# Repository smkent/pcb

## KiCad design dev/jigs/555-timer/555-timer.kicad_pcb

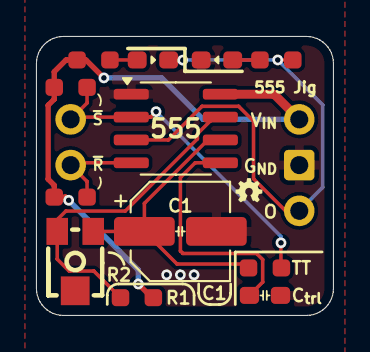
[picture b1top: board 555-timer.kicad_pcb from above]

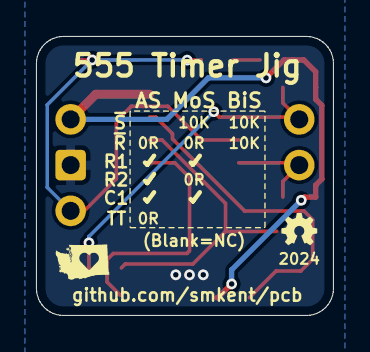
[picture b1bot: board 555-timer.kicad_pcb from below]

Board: 2 copper layers, 16.5 x 15.5 mm, 14 parts (2 on the bottom side), 10 nets.

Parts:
C0: 0u1; C_0603_1608Metric_Pad1.08x0.95mm_HandSolder
C1: 1u; C_Combo_CP_Elec_5x5.4
J1: Pin headers; PinHeader_1x03_P2.54mm_Vertical_simple_pad2gnd
J2: Pin headers; PinHeader_1x02_P2.54mm_Vertical_simple
LED1, LED2: LED_Small; LED_0603_1608Metric_Pad1.05x0.95mm_HandSolder_simple
R0, R3, R4: 0R; R_0603_1608Metric_Pad0.98x0.95mm_HandSolder_simple
R1: 10K; R_0603_1608Metric_Pad0.98x0.95mm_HandSolder_simple
R5, R6: 1K; R_0603_1608Metric_Pad0.98x0.95mm_HandSolder_simple
RV1: 500K; RES-ADJ-SMD_VG039NCH
U1: NE555; SOIC-8_3.9x4.9mm_P1.27mm

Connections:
+5V: J1.1, R0.2, R1.1, R4.2, R5.1, U1.8 (VCC)
GND: C0.2, C1.2, J1.2, LED2.1 (K), U1.1 (GND)
unnamed: LED1.2 (A), R5.2
unnamed: LED2.2 (A), R6.2
unnamed: C0.1, U1.5 (Control)
unnamed: R1.2, RV1.3, U1.7 (Discharge)
unnamed: C1.1, R3.2, RV1.1, U1.6 (Threshold)
Output: J1.3, LED1.1 (K), R6.1, U1.3 (Output)
~R: J2.2, R0.1, U1.4 (~Reset)
~S: J2.1, R3.1, R4.1, U1.2 (Trigger)

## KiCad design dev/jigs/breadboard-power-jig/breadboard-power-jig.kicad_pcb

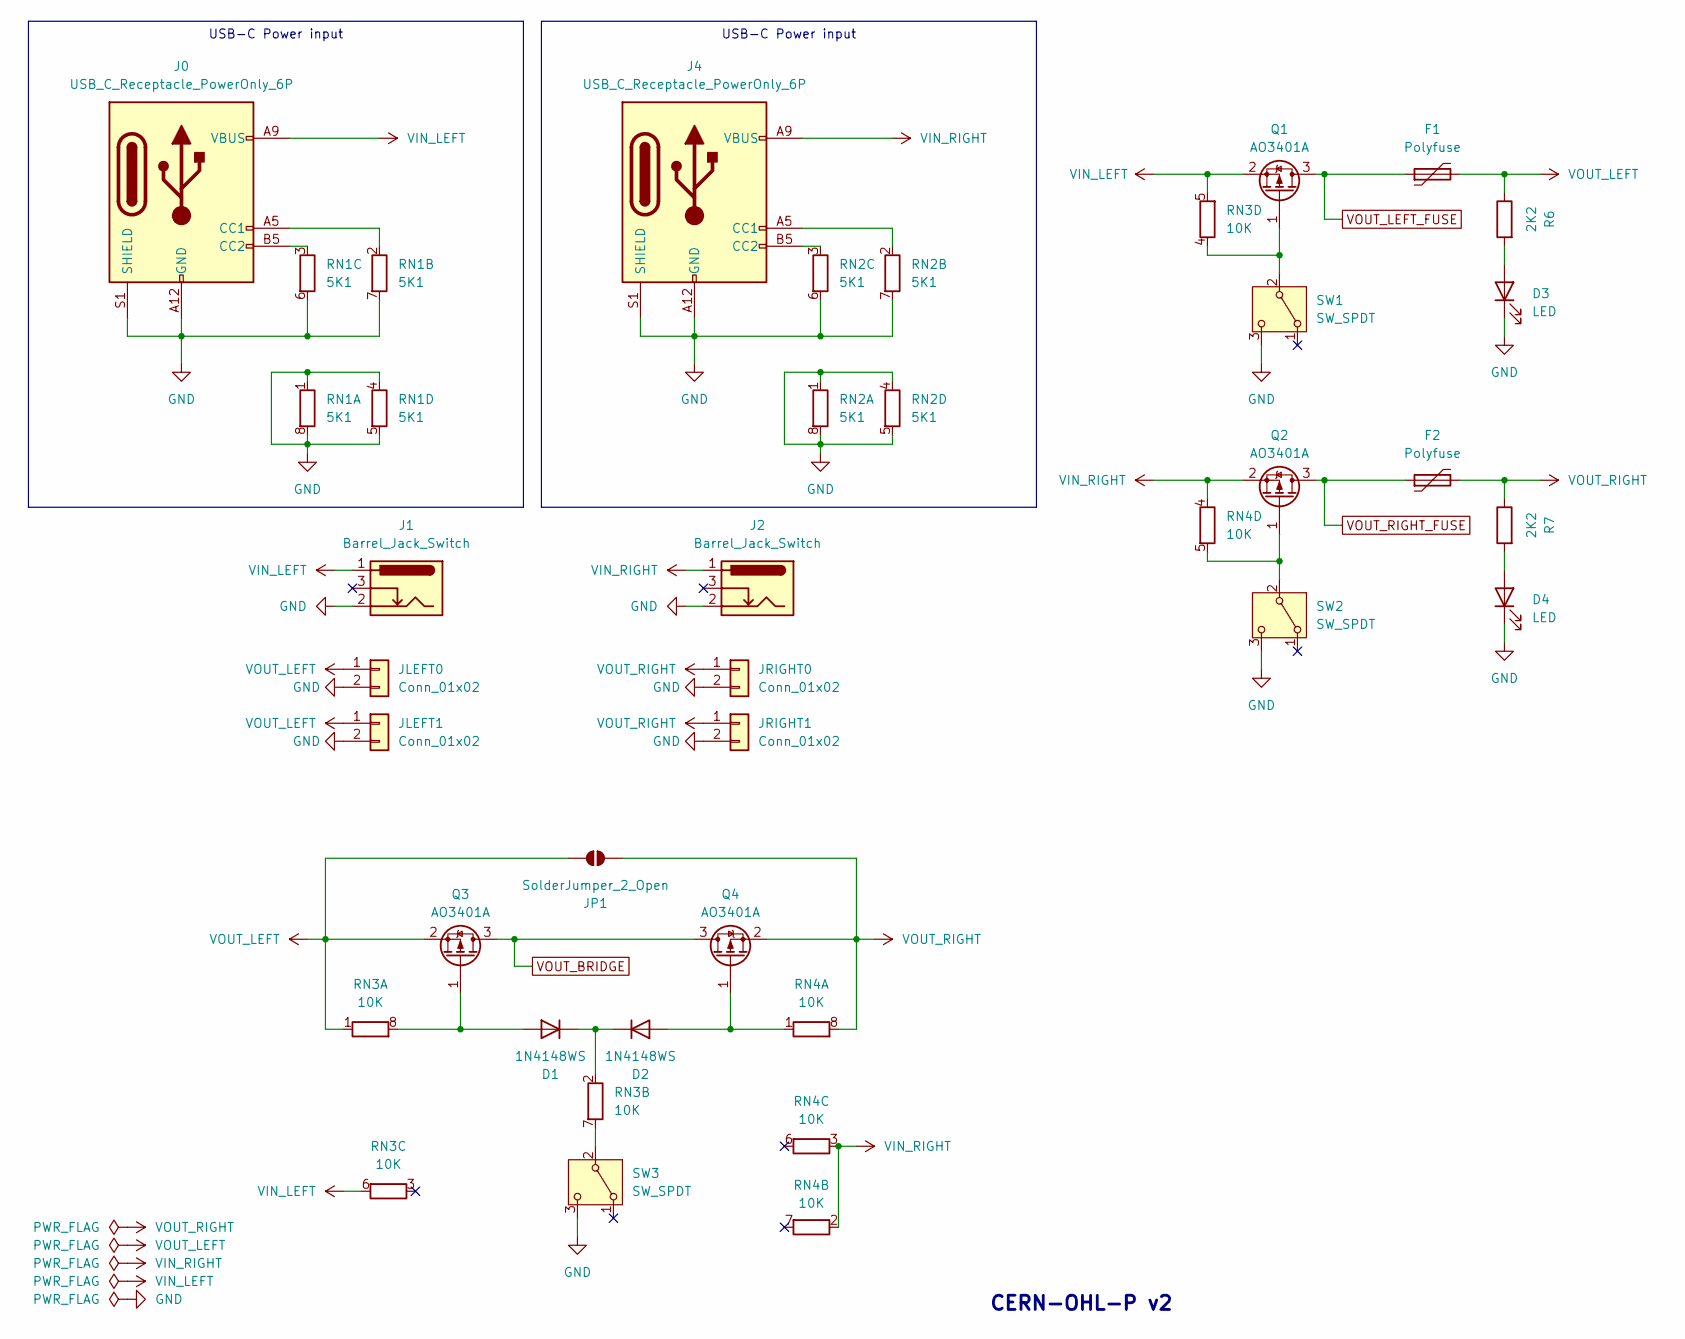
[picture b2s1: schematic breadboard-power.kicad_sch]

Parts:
D1, D2: 1N4148WS; D_SOD-323_HandSoldering_simple
D3, D4: LED; LED_0805_2012Metric_Pad1.15x1.40mm_HandSolder_simple
F1, F2: Polyfuse; Fuse_1206_3216Metric_Pad1.42x1.75mm_HandSolder_simple
J0, J4: USB_C_Receptacle_PowerOnly_6P; USB_C_Receptacle_GCT_USB4125-xx-x_6P_TopMnt_Horizontal_hand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
J1, J2: Barrel_Jack_Switch; Conn_Combo_DC-050_TerminalBlock_JST-XH-2P-horizontal-TH-or-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
JLEFT0, JLEFT1: Conn_01x02; PinHeader_1x02_P2.54mm_Vertical_simple_pad2gnd
JP1: SolderJumper_2_Open; SolderJumper-2_P1.3mm_Open_RoundedPad1.0x1.5mm_simple
JRIGHT0, JRIGHT1: Conn_01x02; PinHeader_1x02_P2.54mm_Vertical_simple_pad2gnd
Q1, Q2, Q3, Q4: AO3401A; SOT-23; LCSC Part C15127
R6, R7: 2K2; R_0805_2012Metric_Pad1.20x1.40mm_HandSolder
RN1, RN2: 5K1; R_Array_Convex_4x0603
RN3, RN4: 10K; R_Array_Convex_4x0603
SW1, SW2: SW_SPDT; SW-TH_DEALON_SS-12D01-GX_simple; LCSC Part C2998803
SW3: SW_SPDT; SW-SMD_3P-P1.50_L2.7-W6.6; LCSC Part C2998803

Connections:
GND: D3.1 (K), D4.1 (K), J0.A12 (GND), J0.B12 (GND), J0.S1 (SHIELD), J1.2, J2.2, J4.A12 (GND), J4.B12 (GND), J4.S1 (SHIELD), JLEFT0.2, JLEFT1.2, JRIGHT0.2, JRIGHT1.2, RN1.1 (R1.1), RN1.4 (R4.1), RN1.5 (R4.2), RN1.6 (R3.2), RN1.7 (R2.2), RN1.8 (R1.2), RN2.1 (R1.1), RN2.4 (R4.1), RN2.5 (R4.2), RN2.6 (R3.2), RN2.7 (R2.2), RN2.8 (R1.2), SW1.3 (C), SW2.3 (C), SW3.3 (C)
unnamed: D1.2 (A), Q3.1 (G), RN3.8 (R1.2)
unnamed: D1.1 (K), D2.1 (K), RN3.2 (R2.1)
unnamed: D2.2 (A), Q4.1 (G), RN4.1 (R1.1)
unnamed: D3.2 (A), R6.2
unnamed: D4.2 (A), R7.2
unnamed: J0.A5 (CC1), RN1.2 (R2.1)
unnamed: J0.B5 (CC2), RN1.3 (R3.1)
unnamed: J4.A5 (CC1), RN2.2 (R2.1)
unnamed: J4.B5 (CC2), RN2.3 (R3.1)
unnamed: Q1.1 (G), RN3.4 (R4.1), SW1.2 (B)
unnamed: Q2.1 (G), RN4.5 (R4.2), SW2.2 (B)
unnamed: RN3.7 (R2.2), SW3.2 (B)
VIN_LEFT: J0.A9 (VBUS), J0.B9 (VBUS), J1.1, Q1.2 (S), RN3.5 (R4.2), RN3.6 (R3.2)
VIN_RIGHT: J2.1, J4.A9 (VBUS), J4.B9 (VBUS), Q2.2 (S), RN4.2 (R2.1), RN4.3 (R3.1), RN4.4 (R4.1)
VOUT_BRIDGE: Q3.3 (D), Q4.3 (D)
VOUT_LEFT: F1.2, JLEFT0.1, JLEFT1.1, JP1.1 (A), Q3.2 (S), R6.1, RN3.1 (R1.1)
VOUT_LEFT_FUSE: F1.1, Q1.3 (D)
VOUT_RIGHT: F2.2, JP1.2 (B), JRIGHT0.1, JRIGHT1.1, Q4.2 (S), R7.1, RN4.8 (R1.2)
VOUT_RIGHT_FUSE: F2.1, Q2.3 (D)

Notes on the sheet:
USB-C Power input
CERN-OHL-P v2

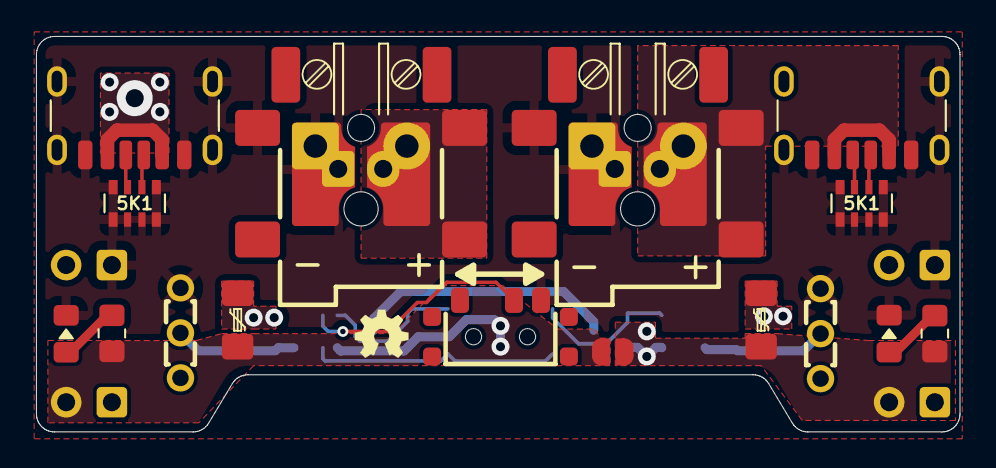
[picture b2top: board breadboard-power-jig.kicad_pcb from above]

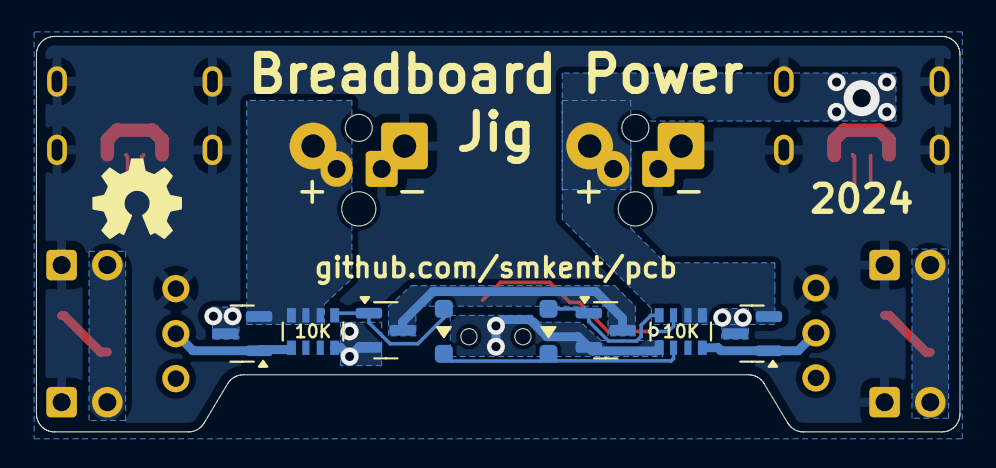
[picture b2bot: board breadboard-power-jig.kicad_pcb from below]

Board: 2 copper layers, 51.3 x 22.0 mm, 28 parts (12 on the bottom side), 20 nets.

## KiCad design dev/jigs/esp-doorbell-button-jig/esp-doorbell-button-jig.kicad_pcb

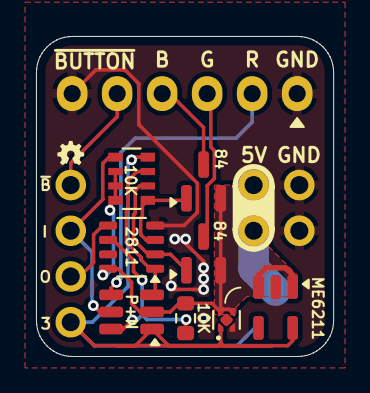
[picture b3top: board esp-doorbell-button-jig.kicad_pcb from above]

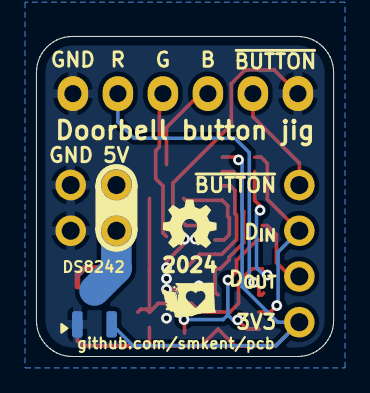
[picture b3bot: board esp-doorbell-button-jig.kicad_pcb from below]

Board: 2 copper layers, 16.5 x 17.8 mm, 12 parts (3 on the bottom side), 13 nets.

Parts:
J1: Pin headers; PinHeader_1x04_P2.54mm_Vertical_simple
J3: JST XH; JST_XH_B6B-XH-A_1x06_P2.50mm_Vertical_slim
J4: Pin Headers; PinHeader_2x02_P2.54mm_Vertical_simple
Q1, Q2: BSS84; SOT-23_simple
Q3: G1NP02LLE; SOT-23-6_simple
R5: 10K; R_0603_1608Metric
RN1: 10K; R_Array_Convex_4x0603
U1: WS2811F; FSOP-8_L3.3-W1.7-P0.80-LS2.9-BL
U2: DS8242-50SS3; SOT-23_simple
U3: Texas_X2SON-4_1x1mm_P0.65mm
U4: ME6211C33M5; SOT-23-5_simple

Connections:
+3V3: J1.4, Q3.1 (G), RN1.4 (R4.1), U2.2 (VO), U3.1, U4.5 (V_{OUT})
+5V: J4.1, J4.3, Q1.2 (S), Q2.2 (S), Q3.2 (S), R5.2, RN1.6 (R3.2), RN1.7 (R2.2), RN1.8 (R1.2), U1.8 (VDD), U2.3 (VI), U3.3, U3.4, U4.1 (V_{IN}), U4.3 (CE)
BUTTON: J1.1, J3.5
BUTTON_LED_B: J3.4, Q1.3 (D)
BUTTON_LED_B_EN: Q1.1 (G), RN1.1 (R1.1), U1.3 (OUTB)
BUTTON_LED_G: J3.3, Q2.3 (D)
BUTTON_LED_G_EN: Q2.1 (G), RN1.2 (R2.1), U1.2 (OUTG)
BUTTON_LED_R: J3.2, Q3.4 (D)
BUTTON_LED_R_EN: Q3.3 (G), RN1.3 (R3.1), U1.1 (OUTR)
DATA_IN: Q3.6 (D), R5.1, U1.6 (DIN)
DATA_IN_3V3: J1.2, Q3.5 (S), RN1.5 (R4.2)
DATA_OUT: J1.3, U1.5 (DO)
GND: J3.1, J3.6, J4.2, J4.4, U1.4 (GND), U2.1 (GND), U3.2, U4.2 (V_{SS})

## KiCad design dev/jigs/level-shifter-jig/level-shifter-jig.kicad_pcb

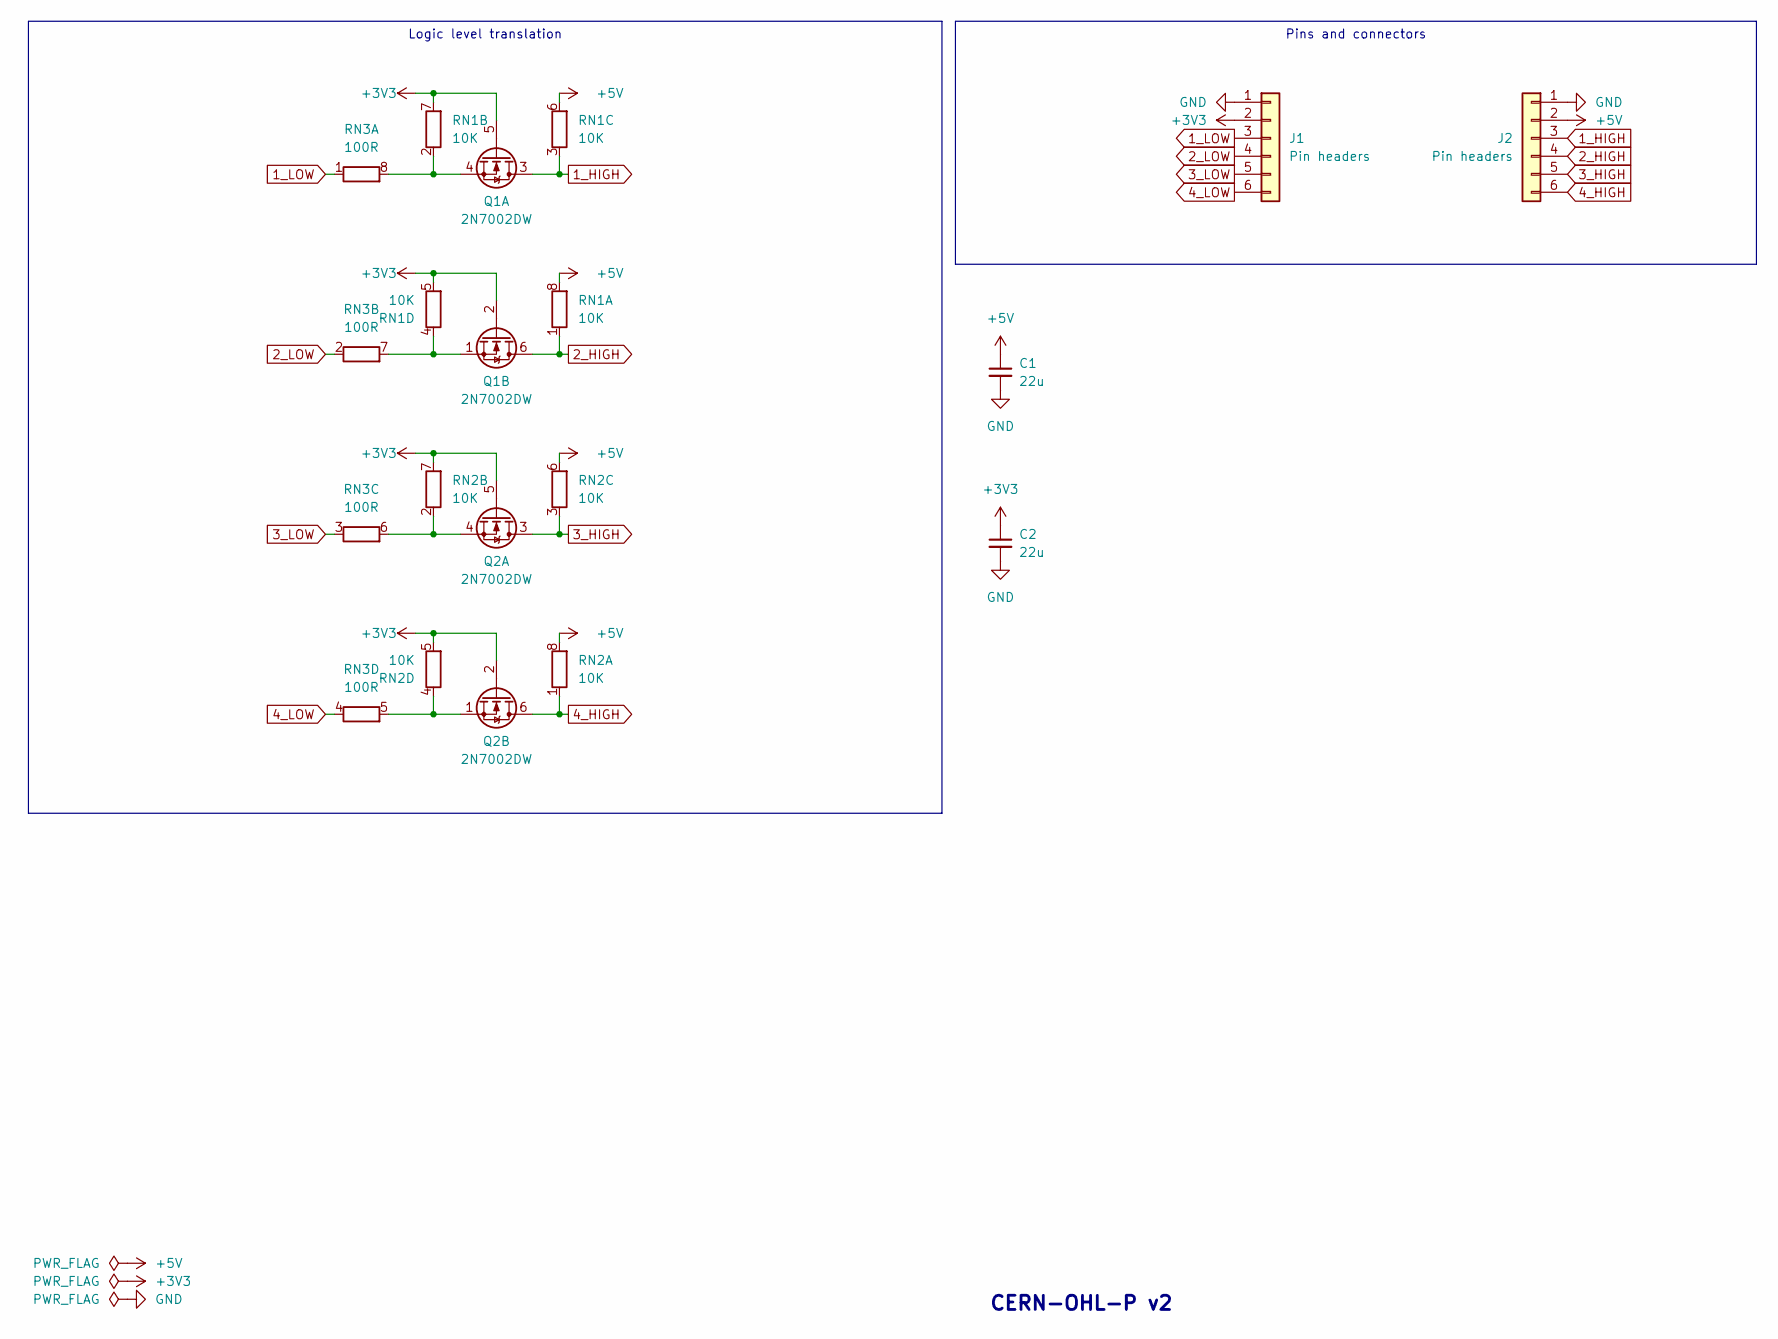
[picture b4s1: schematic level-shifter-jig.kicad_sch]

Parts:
C1, C2: 22u; C_0603_1608Metric_Pad1.08x0.95mm_HandSolder
J1, J2: Pin headers; PinHeader_1x06_P2.54mm_Vertical_simple_pad1gnd
Q1, Q2: 2N7002DW; SOT-363_SC-70-6_simple; LCSC Part C5190214
RN1, RN2: 10K; R_Array_Convex_4x0603
RN3: 100R; R_Array_Convex_4x0603

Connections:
1_HIGH: J2.3, Q1.3 (D), RN1.3 (R3.1)
1_LOW: J1.3, RN3.1 (R1.1)
2_HIGH: J2.4, Q1.6 (D), RN1.1 (R1.1)
2_LOW: J1.4, RN3.2 (R2.1)
3_HIGH: J2.5, Q2.3 (D), RN2.3 (R3.1)
3_LOW: J1.5, RN3.3 (R3.1)
4_HIGH: J2.6, Q2.6 (D), RN2.1 (R1.1)
4_LOW: J1.6, RN3.4 (R4.1)
+3V3: C2.1, J1.2, Q1.2 (G), Q1.5 (G), Q2.2 (G), Q2.5 (G), RN1.5 (R4.2), RN1.7 (R2.2), RN2.5 (R4.2), RN2.7 (R2.2)
+5V: C1.1, J2.2, RN1.6 (R3.2), RN1.8 (R1.2), RN2.6 (R3.2), RN2.8 (R1.2)
GND: C1.2, C2.2, J1.1, J2.1
unnamed: Q1.4 (S), RN1.2 (R2.1), RN3.8 (R1.2)
unnamed: Q1.1 (S), RN1.4 (R4.1), RN3.7 (R2.2)
unnamed: Q2.4 (S), RN2.2 (R2.1), RN3.6 (R3.2)
unnamed: Q2.1 (S), RN2.4 (R4.1), RN3.5 (R4.2)

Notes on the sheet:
Pins and connectors
Logic level translation
CERN-OHL-P v2

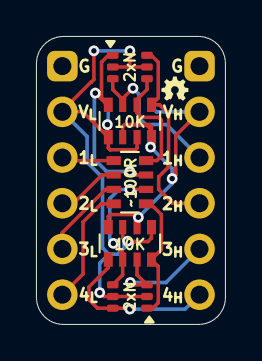
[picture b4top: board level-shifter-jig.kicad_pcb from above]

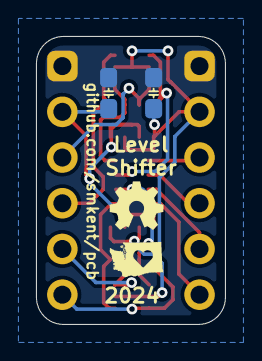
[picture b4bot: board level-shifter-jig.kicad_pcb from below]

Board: 2 copper layers, 10.5 x 16.0 mm, 9 parts (4 on the bottom side), 15 nets.

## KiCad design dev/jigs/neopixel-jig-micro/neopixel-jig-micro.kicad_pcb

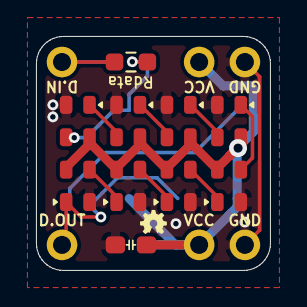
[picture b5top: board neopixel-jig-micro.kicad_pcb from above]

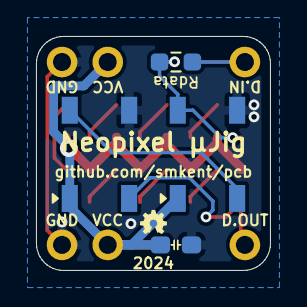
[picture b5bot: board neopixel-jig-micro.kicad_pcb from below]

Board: 2 copper layers, 13.0 x 13.0 mm, 18 parts (8 on the bottom side), 13 nets.

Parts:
C1, C2: 10u; C_0603_1608Metric_Pad1.08x0.95mm_HandSolder
D1, D2: WS2812B; LED_WS2812B_PLCC4_5.0x5.0mm_P3.2mm_simple_small_courtyard
J1, J2: Conn_01x02; PinHeader_1x02_P2.54mm_Vertical_simple
J3, J4: Conn_01x01; PinHeader_1x01_P2.54mm_simple
LED1, LED2, LED3, LED4, LED5, LED6, LED7, LED8: WS2812B-2020; LED-SMD_4P-L2.0-W2.0-BR-1
R1, R2: 100R; R_0603_1608Metric_Pad0.98x0.95mm_HandSolder

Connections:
DATA_2: LED4.1 (DOUT), LED5.3 (DIN)
DATA_IN: D1.4 (DIN), LED1.3 (DIN), R1.2, R2.2
DATA_OUT: D2.2 (DOUT), J4.1, LED8.1 (DOUT)
GND: C1.2, C2.2, D1.3 (VSS), D2.3 (VSS), J1.2, J2.2, LED1.2 (VSS), LED2.2 (VSS), LED3.2 (VSS), LED4.2 (VSS), LED5.2 (VSS), LED6.2 (VSS), LED7.2 (VSS), LED8.2 (VSS)
unnamed: D1.2 (DOUT), D2.4 (DIN)
unnamed: J3.1, R1.1, R2.1
unnamed: LED1.1 (DOUT), LED2.3 (DIN)
unnamed: LED2.1 (DOUT), LED3.3 (DIN)
unnamed: LED3.1 (DOUT), LED4.3 (DIN)
unnamed: LED5.1 (DOUT), LED6.3 (DIN)
unnamed: LED6.1 (DOUT), LED7.3 (DIN)
unnamed: LED7.1 (DOUT), LED8.3 (DIN)
VCC: C1.1, C2.1, D1.1 (VDD), D2.1 (VDD), J1.1, J2.1, LED1.4 (VDD), LED2.4 (VDD), LED3.4 (VDD), LED4.4 (VDD), LED5.4 (VDD), LED6.4 (VDD), LED7.4 (VDD), LED8.4 (VDD)

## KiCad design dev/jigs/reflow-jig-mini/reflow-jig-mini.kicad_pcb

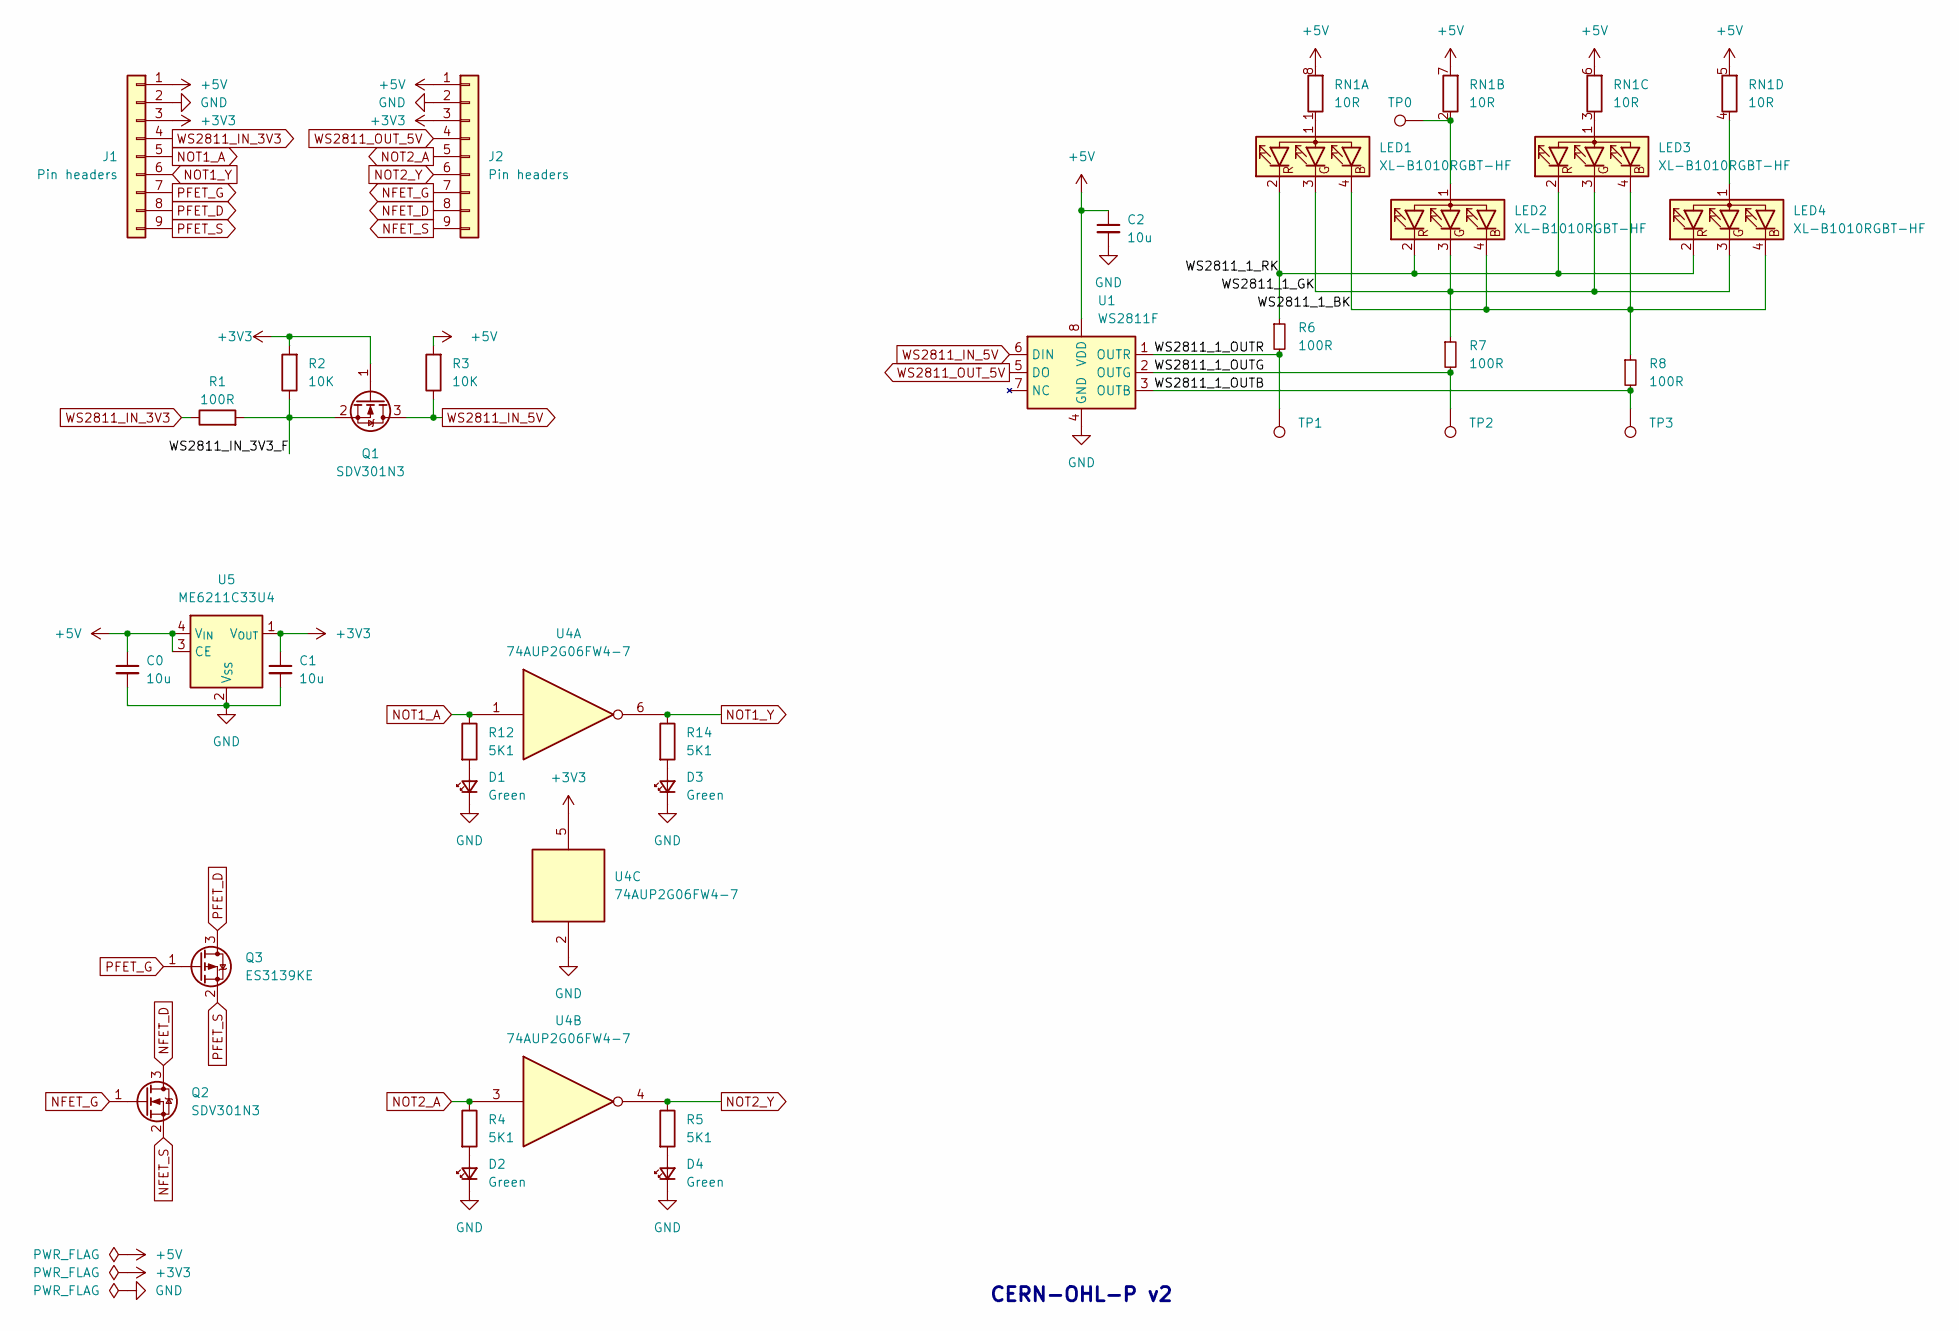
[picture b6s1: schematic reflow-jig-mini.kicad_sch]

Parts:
C0, C1, C2: 10u; C_0402_1005Metric_simple
D1, D2, D3, D4: Green; LED_0402_1005Metric
J1, J2: Pin headers; PinHeader_1x09_P2.54mm_Vertical_simple
LED1, LED2, LED3, LED4: XL-B1010RGBT-HF; LED-ARRAY-SMD_4P-L1.0-W1.0-TR-RD
Q1, Q2: SDV301N3; DFN1006-3; LCSC Part C5334596
Q3: ES3139KE; DFN1006-3; LCSC Part C7527987
R1: 100R; R_0402_1005Metric
R2, R3: 10K; R_0402_1005Metric
R4, R5, R12, R14: 5K1; R_0402_1005Metric
R6, R7, R8: 100R; R_0603_1608Metric_simple
RN1: 10R; R_Array_Convex_4x0603
TP0, TP1, TP2, TP3: TestPoint; TestPoint_Pad_D1.0mm
U1: WS2811F; FSOP-8_L3.3-W1.7-P0.80-LS2.9-BL; LCSC Part C5446692
U4: 74AUP2G06FW4-7; X2-DFN1010-6_L1.0-W1.0-P0.35-BL; LCSC Part C842402
U5: ME6211C33U4; UDFN-4-1EP_1x1mm_P0.65mm_EP0.48x0.48mm; LCSC Part C428904

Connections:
+3V3: C1.1, J1.3, J2.3, Q1.1 (G), R2.2, U4.5 (VCC), U5.1 (V_{OUT})
+5V: C0.1, C2.1, J1.1, J2.1, R3.2, RN1.5 (R4.2), RN1.6 (R3.2), RN1.7 (R2.2), RN1.8 (R1.2), U1.8 (VDD), U5.3 (CE), U5.4 (V_{IN})
/WS2811_1_BK: LED1.4 (BK), LED2.4 (BK), LED3.4 (BK), LED4.4 (BK), R8.1
/WS2811_1_GK: LED1.3 (GK), LED2.3 (GK), LED3.3 (GK), LED4.3 (GK), R7.1
/WS2811_1_OUTB: R8.2, TP3.1, U1.3 (OUTB)
/WS2811_1_OUTG: R7.2, TP2.1, U1.2 (OUTG)
/WS2811_1_OUTR: R6.2, TP1.1, U1.1 (OUTR)
/WS2811_1_RK: LED1.2 (RK), LED2.2 (RK), LED3.2 (RK), LED4.2 (RK), R6.1
/WS2811_IN_3V3_F: Q1.2 (S), R1.2, R2.1
GND: C0.2, C1.2, C2.2, D1.1 (K), D2.1 (K), D3.1 (K), D4.1 (K), J1.2, J2.2, U1.4 (GND), U4.2 (GND), U5.2 (V_{SS})
NFET_D: J2.8, Q2.3 (D)
NFET_G: J2.7, Q2.1 (G)
NFET_S: J2.9, Q2.2 (S)
NOT1_A: J1.5, R12.1, U4.1 (1A)
NOT1_Y: J1.6, R14.1, U4.6 (1Y)
NOT2_A: J2.5, R4.1, U4.3 (2A)
NOT2_Y: J2.6, R5.1, U4.4 (2Y)
unnamed: D1.2 (A), R12.2
unnamed: D2.2 (A), R4.2
unnamed: D3.2 (A), R14.2
unnamed: D4.2 (A), R5.2
unnamed: LED1.1 (A), RN1.1 (R1.1)
unnamed: LED2.1 (A), RN1.2 (R2.1), TP0.1
unnamed: LED3.1 (A), RN1.3 (R3.1)
unnamed: LED4.1 (A), RN1.4 (R4.1)
PFET_D: J1.8, Q3.3 (D)
PFET_G: J1.7, Q3.1 (G)
PFET_S: J1.9, Q3.2 (S)
WS2811_IN_3V3: J1.4, R1.1
WS2811_IN_5V: Q1.3 (D), R3.1, U1.6 (DIN)
WS2811_OUT_5V: J2.4, U1.5 (DO)

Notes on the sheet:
CERN-OHL-P v2

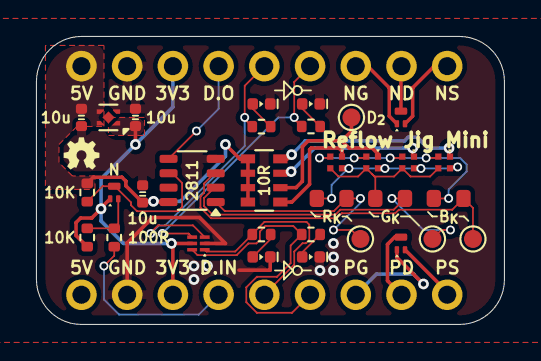
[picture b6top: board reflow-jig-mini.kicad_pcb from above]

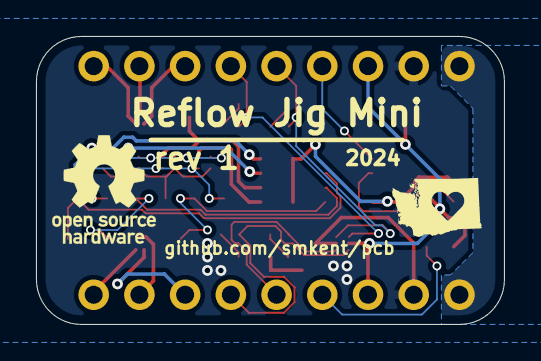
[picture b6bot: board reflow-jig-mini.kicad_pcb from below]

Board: 2 copper layers, 26.0 x 16.0 mm, 34 parts (2 on the bottom side), 31 nets.
